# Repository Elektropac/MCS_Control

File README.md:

# MCS Control Firmware

Firmware til MCS Control-modulet.

## Hardware (v1)

- **Board:** Waveshare ESP32-S3-ETH
- **Chip:** ESP32-S3R8 (dual-core 240MHz, 512KB SRAM, 8MB PSRAM OPI)
- **Flash:** 16MB (W25Q128, QIO)
- **Ethernet:** W5500 via SPI (GPIO 11/12/13/14, RST=9, INT=10)
- **USB:** Type-C med CDC (upload + serial debug)
- **Produkt-link:** https://www.waveshare.com/esp32-s3-eth.htm
- **Wiki:** https://www.waveshare.com/wiki/ESP32-S3-ETH

## I2C Devices

| Address | Chip | Funktion |
|---------|------|----------|
| 0x21 | TCA9535 | Voltage select (5V/12V/24V) + HW/module version |
| 0x23 | TCA9535 | Input config channel B (analog front-end switches) |
| 0x25 | TCA9535 | Input config channel A (analog front-end switches) |
| 0x27 | TCA9535 | Serial control (RS-232/RS-485) + 2x relæ |
| 0x48 | ADS1115 | 16-bit ADC channel A (A1–A4) |
| 0x49 | ADS1115 | 16-bit ADC channel B (B1–B4) |

## Projektstruktur

```
src/
├── main.cpp              ← setup + FreeRTOS task start
├── board/                ← pin-definitions, board-specifikt
├── sampler/              ← 4 kHz ISR pulse sampling + flow guard
├── logging/              ← leveled log system (serial + ringbuffer)
├── debug/                ← diagnostik, serial commands, task registry
└── drivers/              ← hardware drivers
    ├── all_drivers_init  ← init af alt med probe + fejlhåndtering
    ├── hw_status         ← centralt register over hvad der er online
    ├── i2c               ← bus init + probe
    ├── voltage_select    ← spændingsvalg via 74HC139 demux
    ├── version           ← hardware + module version readout
    ├── serial_control    ← RS-232/RS-485 mode-skift
    ├── relays            ← 2x relæ kontrol
    ├── input_config      ← analog front-end switch kontrol
    ├── adc               ← ADS1115 voltage/mA/differential måling
    ├── buttons           ← 5-knap analog ladder
    ├── buzzer            ← PWM toner + melodier
    └── oled              ← SSD1306 128x64 display
```

## Arkitektur

### FreeRTOS (ikke custom scheduler)
Alt kører som selvstændige FreeRTOS tasks. Arduino's `loop()` er suspenderet.
FreeRTOS er standard på ESP32 og veldokumenteret — nemt for alle at læse op på.

### Memory-strategi
| Type | Bruges til |
|------|-----------|
| Intern SRAM (320 KB) | Tidskritisk: sampler, flow guard, drivers, task stacks |
| PSRAM (8 MB) | Ikke-tidskritisk: JSON parsing, interface-buffere (Niklas), store data |
| LittleFS (flash) | Persistent config (overlever genstart) |

Beslutning: Interface-laget (JSON kommunikation mellem Jesper/Niklas) allokerer buffere i PSRAM via `ps_malloc()`.
Tidskritisk kode bruger kun intern RAM.

### Memory reference

| Type | Størrelse | Hastighed | Volatile | Bruges til |
|------|-----------|-----------|----------|-----------|
| Internal SRAM | 320 KB | 1 clock cycle | Ja | Task stacks, variabler, buffere, FreeRTOS kernel |
| PSRAM (OPI) | 8 MB | ~10x langsommere (SPI) | Ja | Store buffere, JSON, data der ikke er tidskritisk |
| RTC SRAM | 16 KB | Hurtig | Overlever deep sleep | Variabler der skal overleve sleep (wake-up state) |
| Flash (XIP) | 16 MB | Langsom (cachet) | Nej | Firmware, LittleFS, NVS, OTA partitions |
| ↳ LittleFS | 5.8 MB | " | Nej | Filer (config JSON, logs, assets) |
| ↳ NVS | ~20 KB | " | Nej | Key-value store (WiFi creds, små config-værdier) |
| eFuse | 256 bytes | Engangslæs | Nej, permanent | MAC-adresse, security keys (read-only) |

**Tommelfingerregler:**
- Skal det være hurtigt → intern SRAM
- Skal det være stort → PSRAM
- Skal det overleve genstart → Flash (LittleFS eller NVS)
- Skal det overleve deep sleep → RTC SRAM

**Eksempler:**

```cpp
// --- Intern SRAM (default, alt normalt) ---
uint8_t buffer[256];                    // stack — automatisk intern
char* ptr = (char*)malloc(1024);        // heap — automatisk intern

// --- PSRAM (store ting, ikke tidskritisk) ---
char* json_buf = (char*)ps_malloc(8192);              // allokér 8 KB i PSRAM
uint8_t* big = (uint8_t*)heap_caps_malloc(50000, MALLOC_CAP_SPIRAM);  // eksplicit PSRAM

// --- RTC SRAM (overlever deep sleep) ---
RTC_DATA_ATTR uint32_t boot_count = 0;  // bevares gennem deep sleep cycles

// --- LittleFS (filer i flash, overlever genstart) ---
#include <LittleFS.h>
LittleFS.begin();
File f = LittleFS.open("/config.json", "r");
String content = f.readString();
f.close();

// --- NVS (key-value, overlever genstart) ---
#include <Preferences.h>
Preferences prefs;
prefs.begin("config", false);           // namespace "config"
prefs.putString("ssid", "MyWiFi");      // skriv
String ssid = prefs.getString("ssid");  // læs
prefs.end();
```

### TBD
- [ ] PSRAM-allocator til ArduinoJson — så `JsonDocument` automatisk bruger PSRAM uden rå pointers
- [ ] Function_silo: Byg kommando-register ud (relay_set, voltage_set, input_mode, adc_read, serial_mode, status, config_get/set)

## Toolchain

- PlatformIO (VS Code)
- Framework: Arduino
- Partition: Dual OTA (2x 5MB app) + LittleFS (5.8MB)

## Ansvarsfordeling

- **Jesper:** Hardware-lag — I/O, pulsmåling, relæer, sensorer, OLED/menu, lokal config/storage
- **Niklas:** Kommunikation — WiFi, Ethernet, BLE, USB serial, ESP-NOW, server-forbindelse

## Fejltolerance

Alle I2C-drivers probes ved boot. Hvis en chip ikke svarer:
- Den logges som fejl
- `hw_available()` returnerer false
- Driver-funktioner returnerer tidligt (0 / no-op)
- Systemet kører videre med det der virker

## Byg

1. Åbn mappen i VS Code med PlatformIO installeret
2. Build (flueben i bunden eller `pio run`)
3. Upload til board (pil i bunden eller `pio run -t upload`)
4. Serial Monitor: 115200 baud

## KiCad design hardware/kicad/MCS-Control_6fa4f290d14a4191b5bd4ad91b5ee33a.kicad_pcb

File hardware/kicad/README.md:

## PoE forenklet 2026-09-28

Ét nyt ark: **PoE_5V**, 5 V med mål op til 2 A, tegnet med direkte ledninger. De tidligere 5/12/24 V-ark er arkiveret i backup/PoE-41W-revA. PCB er uændret. Læs [PoE-design.md](PoE-design.md) om integration og resterende hardwarevalidering.

## DRC-oprydning efter import (2026-11-04, branch `hw/drc-oprydning`)

`hardware/tools/fix_easyeda_import.py` rydder importrester på BottomBoard uden at ændre forbindelser
(alle 938 pads har samme net før/efter; 0 uforbundne). DRC: **1352 → 522 fund**.

- Clearance-regel 0,15 mm (layoutet er lavet med EasyEDA's 6 mil) og kobber-til-kant 0,3 mm.
- 106 bundkomponenter havde courtyard på forsidens lag → flyttet til B.Courtyard.
- 312 pads (alle passive R/C/SD0805) havde pasta-margin −100 mm = ingen stencil-åbning → nulstillet.
- 14 spor med længde 0 fjernet.
- Relæspor (5 mm) `B_RELAY_NO`/`B_RELAY_COM` lå 0,14/0,20 mm fra højre kant → lodrette stykker rykket 0,5 mm ind (nu ~0,65/0,70 mm). DRC: **516 fund**, 0 kobber-til-kant.

**3D-visning rettet** (`hardware/tools/fix_3d_models.py`, kun model-felter):
- 18 PhotoMOS (SMD-8) manglede model på printet (kun sat i biblioteket) → tilføjet.
- 6 DC/DC (SIP-4 B2405S) pegede på en kopi af pin-header-modellen → KiCads Murata CRE1 (samme SIP-4-hus).
- EasyEDA placerer modeller efter midtpunkt, KiCad efter nulpunkt → klemrække U61, header J1, DC/DC drejet/flyttet
  så modellen dækker pads og courtyard.
- Relæ K1/K3 (EasyEDA-model ufuldstændig) og CN1/CN2 (model viste flerpolet klemme) → **forenklede kasser**
  i silketryk-omridsets mål (`3d/*.wrl`). Højde er skøn: relæ 20 mm, klemme 12 mm.
- **SMD-rotationer:** importen havde drejet mange modeller 90/180° (alle 144 R0603, 18 PhotoMOS, SOIC, SSOP,
  SMD-16, 6 SOT-23 på bunden). Rettet ved at finde den drejning hvor modellens benfødder (nederste
  STEP-hjørnepunkter) lander på pads — efterkontrol: 88–100 % for alle typer (SOP-4/SOP-8 kontrolleret visuelt).
- **U24 Waveshare ESP32-S3-ETH:** model tilføjet (`3d/waveshare_esp32s3eth.wrl`, fra control-emulator) — antager
  samme montering som pumpesimulatoren: ben loddet med 2,5 mm afstand, RJ45-siden op, USB ved printkanten.
- **LS1 buzzer (CPT-1667):** forenklet cylinder Ø16,6 mm, højde 8 mm (skøn).

**Tilbage — kræver manuel gennemgang:**
- **⚠ Isolationsslids mangler (250 V AC):** kom ikke med fra EasyEDA som udfræsning. I KiCad ligger kun
  midterlinjen på laget `IsolationSlot` (User.2, fræses IKKE) + HV-grænsen på bottom silk.
  Skal laves som **lukket udskæring på Edge.Cuts, 2 mm bred, runde ender**, langs IsolationSlot-stien:
  (169,09;155,12) → (169,09;149,41) → (176,45;142,04) → (176,45;140,65) → (178,99;138,10) → (178,99;133,79)
  → (182,80;129,98) → (182,80;91,24) → (184,58;89,46) → (193,47;89,46). Går bevidst ikke ud til kanten
  (4,9 mm fra underkant, 6,5 mm fra højre kant).
  Måling med slids: `A_RELAY_NO` ↔ `9-36V_IN` kun **2,56 mm luftafstand** hen over slidsen ved (170,7;152,1) —
  under typisk 3,0 mm for forstærket isolation → flyt 9-36V_IN-sporet ~0,5 mm. Øvrige HV↔LV ≥ 3,5 mm over
  slidsen; uden slids imellem ≥ 9,5 mm.
- 83 courtyard-overlap — **ACCEPTERET (beslutning 2026-11-04, Jesper):** courtyards er normale (~0,27 mm margin),
  komponenterne står reelt tæt: 0,30–0,5 mm pad-til-pad (ingen under 0,3 mm), kobber overholder 0,15 mm clearance.
  Printet er produceret og virker med denne placering → ingen flytning. Tætteste: D13/D14, D3/D4 (0,30 mm), R11/U20, R79/U44 (0,35 mm).
  Markeret som accepteret i `MCS-Control_…kicad_dru` (én regel pr. par, `severity ignore`). Nye overlap fanges stadig. DRC: **433 fund** (kun silk/kosmetik + 12 løse spor).
- 10× SOT-23 (2N7002) har courtyard *mindre* end egne pads (importfejl) — skjuler evt. overlap, giver ikke falske fund.
- 12 spor med løs ende (ikke fjernet automatisk — flere spor har samme net/længde, så en automatisk match kan ramme forkert).
- ~420 silk-advarsler og 2 tekst-tykkelser (kosmetisk).

# MCS-Control i KiCad

**Seneste ændring:** Sheet_3 er nu erstattet af et nyt W5500/Ethernet-diagram med 52 komponenter efter Waveshares reference. Det er udeladt fra PCB. Se [W5500-Sheet_3.md](W5500-Sheet_3.md) for omfang, grænseflade og kontrol. De øvrige ark og begge PCB-filer er uændrede. Importstatus nedenfor beskriver versionen før denne ændring.

Åbn `MCS-Control_6fa4f290d14a4191b5bd4ad91b5ee33a.kicad_pro`, og start Schematic Editor. Dobbeltklik på arkene i venstre side.

Projektet er importeret fra EasyEDA-backuppen den 28. september 2026. Alle syv kildeark er med samt et KiCad-oversigtsark. Sheet_2 var tomt i originalen; IO Expander indeholder en referencetabel som billede.

## Gennemført

- 276 komponenter overført med referencer og værdier.
- Lokale symbolbiblioteker og footprintbibliotek ligger i projektmappen.
- Siderammer og placering er tilpasset KiCad.
- Alle 973 tilsluttede ben i EasyEDAs officielle Protel-netliste har præcis samme forbindelsesgrupper i KiCad. KiCad viser desuden 66 isolerede ben.
- 274 komponenter har fået footprinttilknytning: 264 fra de oprindelige printlayouts og 10 modstande/kondensatorer genbruger samme kildes package-type. Padnumrene for de 264 direkte matches er kontrolleret mod symbolerne.
- BottomBoard er filen med projektets lange navn og endelsen `.kicad_pcb`. TopBoard er `Sapphire_Topboard.kicad_pcb`.

## Udestår før produktion eller automatisk PCB-opdatering

U32 (W5500) og X2 (25 MHz krystal) mangler footprints; de findes ikke på de to kildeprint. Der er ikke valgt erstatninger uden package-verifikation.

ERC giver 759 fund: 704 pin-type-konflikter, 29 uforbundne ben, 8 forsyningsben uden driver, 6 isolerede pin-labels, 6 ben uden driver, 4 netnavnekonflikter og 2 løse labels. Mange importerede symbolben har uspecificeret elektrisk type. Fundene er bevaret til elektrisk gennemgang; de er ikke skjult ved vilkårlige ændringer af pin-typer. Se `Importkontrol-ERC.rpt`.

Netlistematch dokumenterer bevarede forbindelser, ikke at originalkredsløbet er elektrisk korrekt. De to PCB-filer er importerede layouts; DRC, fremstillingsdata og diagram-til-PCB-synkronisering er ikke valideret. Diagrammet omfatter begge print, og komponentfordelingen skal håndteres inden brug af Update PCB from Schematic.

Behold hele mappen samlet, så de relative biblioteksstier virker.

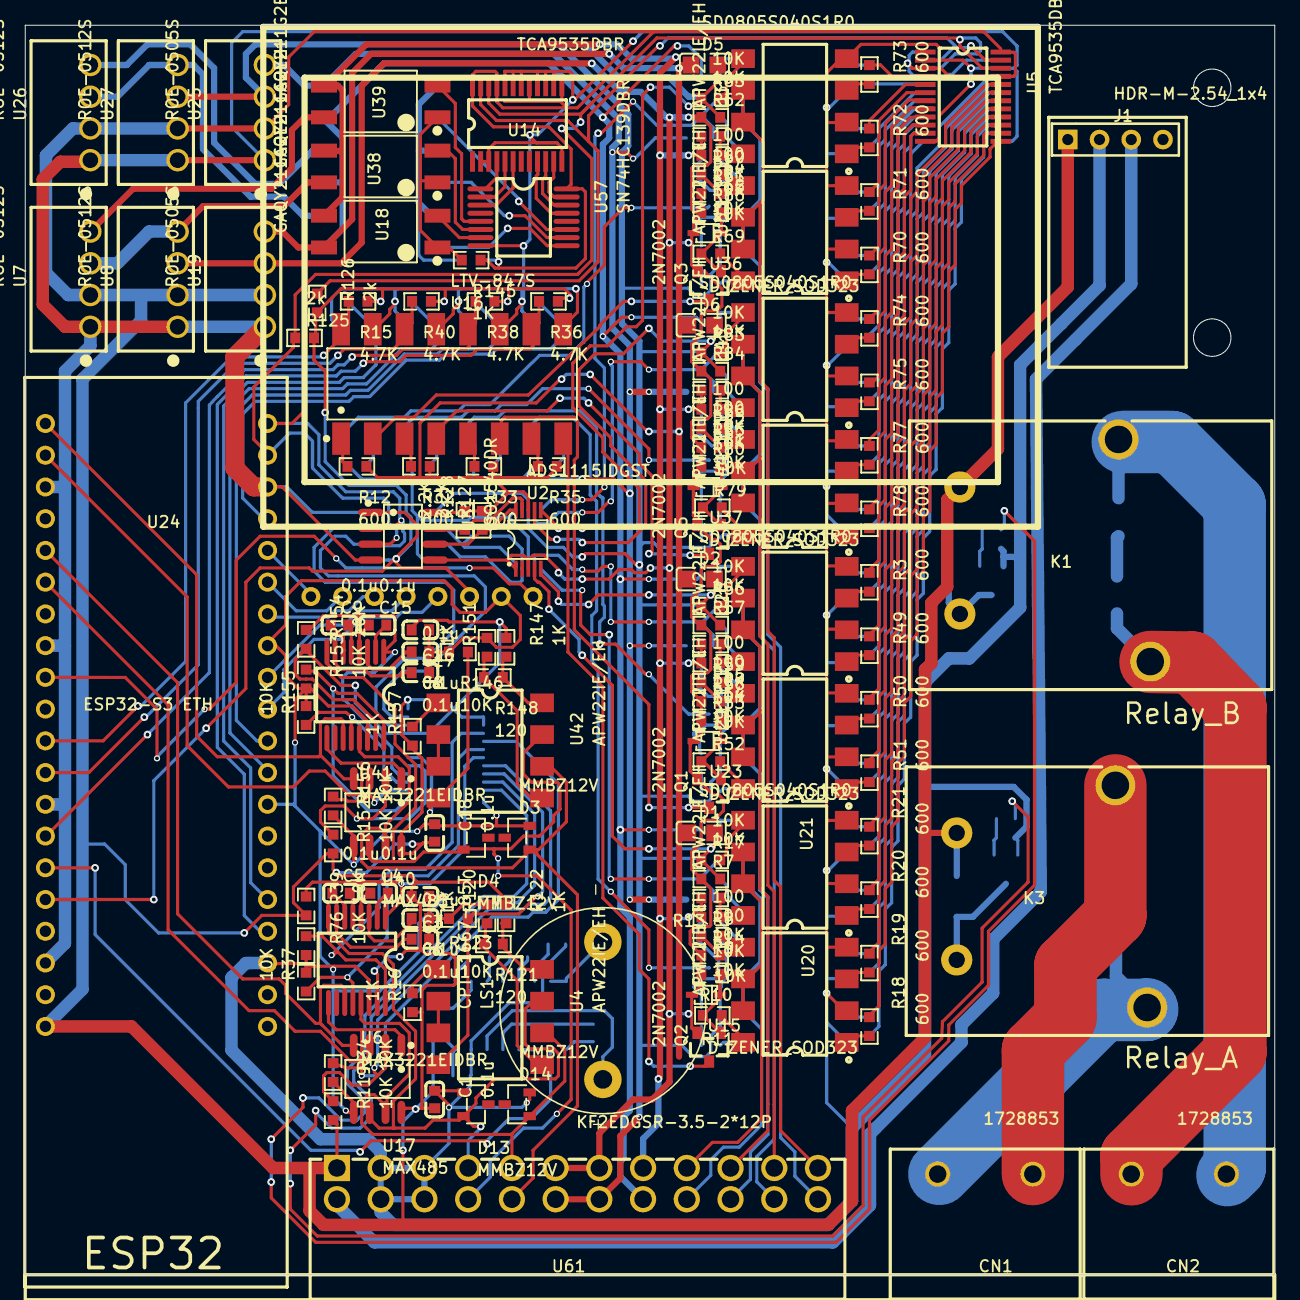
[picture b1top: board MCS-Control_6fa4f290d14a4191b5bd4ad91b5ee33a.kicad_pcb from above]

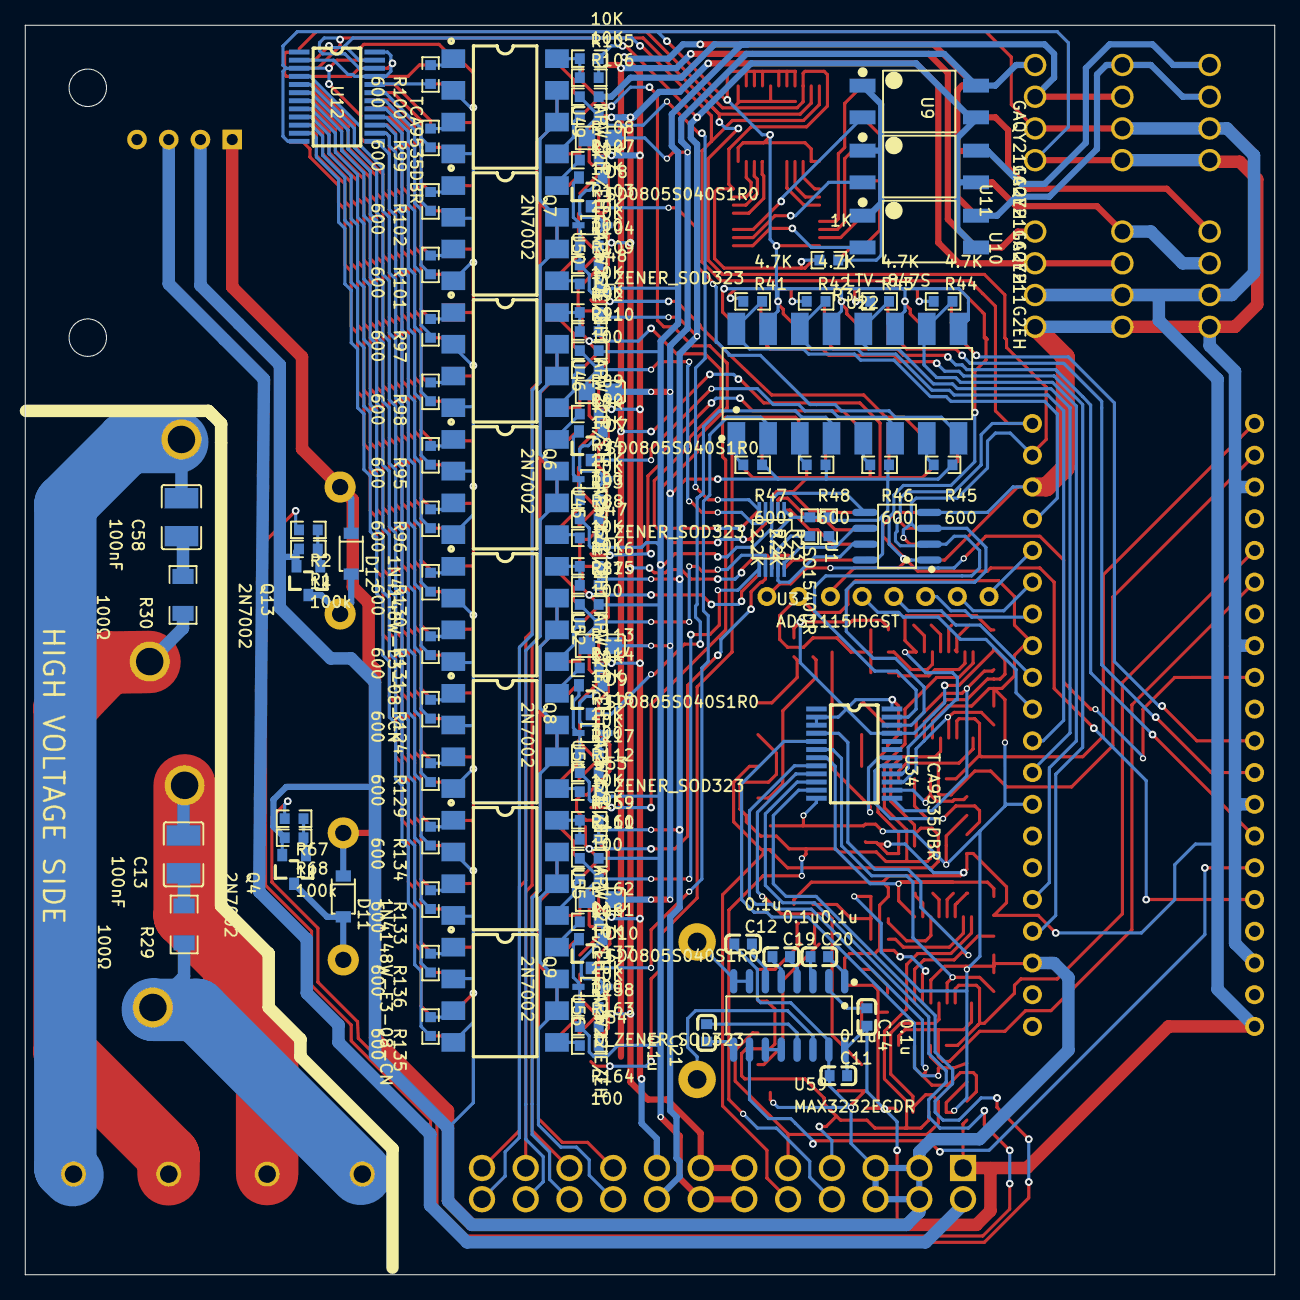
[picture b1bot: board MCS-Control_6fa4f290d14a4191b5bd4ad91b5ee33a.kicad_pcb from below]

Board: 2 copper layers, 100.0 x 100.0 mm, 262 parts (106 on the bottom side), 256 nets.

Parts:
C1, C2, C3, C4, C5, C6, C8, C9, C11, C12, C14, C15, C16, C17, C18, C19, C20, C21: 0.1u; C0603
C13, C58: 100nF; C1210
CN1, CN2: 1728853; CONN-TH_2P-P7.62_1728853
D1, D2, D5, D6, D7, D8, D9, D10: SD0805S040S1R0; D0805-RD
D3, D4, D13, D14: MMBZ12V; SOT-23-3_L2.9-W1.3-P1.90-LS2.4-BR
D11, D12: 1N4148W-E3-08-CN; SOD-123_L2.7-W1.6-LS3.7-RD
Hole_gge434084: Hole_gge434084
Hole_gge434114: Hole_gge434114
J1: HDR-M-2.54_1x4; HDR-M-2.54_1X4
K1, K3: T9GV1L14-5; RELAY-TH_TE_T9GV1L14-9
LS1: CPT-1667-85T; XDCR_CPT-1667-85T
Pad_gge404992: Pad_gge404992
Pad_gge405037: Pad_gge405037
Pad_gge405061: Pad_gge405061
Pad_gge405085: Pad_gge405085
Pad_gge405109: Pad_gge405109
Pad_gge405133: Pad_gge405133
Pad_gge405157: Pad_gge405157
Pad_gge405181: Pad_gge405181
Q1, Q2, Q3, Q4, Q5, Q6, Q7, Q8, Q9, Q13: 2N7002; SOT-23_L2.9-W1.3-P0.95-LS2.4-BR
R1, R68: 100k; R0603
R2, R67: 1k; R0603
R3, R12, R18, R19, R20, R21, R32, R33, R35, R45, R46, R47, R48, R49, R50, R51, R70, R71, R72, R73, R74, R75, R77, R78, R95, R96, R97, R98, R99, R100, R101, R102, R124, R129, R130, R131, R133, R134, R135, R136: 600; R0603
R7, R9, R10, R11, R13, R17, R34, R37, R39, R52, R53, R54, R55, R56, R57, R62, R63, R64, R65, R66, R69, R76, R79, R80, R81, R82, R83, R84, R89, R90, R91, R92, R93, R94, R103, R104, R105, R106, R107, R108, R113, R114, R115, R116, R117, R118, R119, R123, R137, R146, R152, R153, R154, R155, R156, R158, R159, R160, R161, R162: 10K; R0603
R8, R14, R58, R59, R60, R61, R85, R86, R87, R88, R109, R110, R111, R112, R163, R164: 100; R0603
R15, R36, R38, R40, R41, R42, R43, R44: 4.7K; R0603
R16, R31, R120, R122, R145, R147, R151, R157: 1K; R0603
R22, R23, R127, R128: 2.2K; R0603
R29, R30: 100Ω; R1206
R121, R148: 120; R0603
R125, R126: 2k; R0603
U1, U31: ISO1540DR; SOIC-8_L4.9-W3.9-P1.27-LS6.0-BL
U2, U3: ADS1115IDGST; VSSOP-10_L3.0-W3.0-P0.50-LS4.9-BL
U4, U20, U21, U28, U29, U33, U35, U42, U43, U44, U45, U46, U49, U50, U51, U52, U55, U56: APW22IE/EH; SMD-8_L9.8-W6.4-APW212G2EH
U5, U12, U14, U34: TCA9535DBR; TSSOP-24_L7.8-W4.4-P0.65-LS6.4-BL
U6, U41: MAX3221EIDBR; SSOP-16_L6.2-W5.3-P0.65-LS7.8-BL
U7, U8, U26, U27: ROE-0512S; SIP-4_L11.5-W6.0-P2.54-L_ROE-XXXXS
U9, U10, U11, U18, U38, U39: GAQY211G2EH; SOP-4_L6.4-W4.8-P2.54-LS10.2-BL
U15, U23, U36, U37, U47, U48, U53, U54: D_ZENER_SOD323; SOD-323_L1.6-W1.2-LS2.6-RD
U16, U22: LTV-847S; SMD-16_L20.0-W6.5-P2.54-LS10.2-BL
U17, U40: MAX485; SOP-8_L4.9-W3.9-P1.27-LS6.0-BL
U19, U25: ROE-0505S; SIP-4_L11.5-W6.0-P2.54-L_ROE-XXXXS
U24: ESP32-S3 ETH
U57: SN74HC139DBR; SSOP-16_L6.2-W5.3-P0.65-LS7.8-BL
U59: MAX3232ECDR; SOIC-16_L9.9-W3.9-P1.27-LS6.0-BL
U61: KF2EDGSR-3.5-2*12P; CONN-TH_24P-P3.50_KEFA_KF2EDGSR-3.5-2X12P

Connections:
9-36V_IN: J1.3, U61.2
+3V3: Pad_gge405133.1, R15.1, R36.1, R38.1, R40.1, R41.1, R42.1, R43.1, R44.1, R125.2, R126.2, U1.1, U24.36, U31.1
+5V: C1.2, C2.2, C11.2, C14.2, C17.2, C18.2, D11.1, D12.1, J1.1, K1.2, K3.2, R16.1, R31.1, R39.2, R119.2, R122.1, R145.1, R147.1, R152.2, R154.2, R157.1, U5.3, U5.21, U5.24, U6.15, U7.2, U8.2, U12.2, U12.21, U12.24, U14.13, U14.17, U14.21, U14.24, U17.8, U19.2, U24.40, U25.2, U26.2, U27.2, U34.2, U34.3, U34.21, U34.24, U40.8, U41.15, U57.16, U59.16, U61.1
A1_ANALOG_ADC: D1.2, R7.2, R17.1, U2.4
A1_DIGITAL_ISO: Q2.3, U16.8
A1_DIGITAL_MCU: R36.2, U16.10, U24.4
A1_FIELD_IN: U20.6, U20.7, U21.6, U21.7, U61.17
A1_SEL_ANALOG: R21.1, U5.16
A1_SEL_DIGITAL: R18.1, U5.13
A1_SEL_PULLUP: R20.1, U5.15
A1_SEL_SHUNT: R19.1, U5.14
A2_ANALOG_ADC: D2.2, R56.1, R57.2, U2.5
A2_DIGITAL_ISO: Q1.3, U16.6
A2_DIGITAL_MCU: R38.2, U16.12, U24.34
A2_FIELD_IN: U28.6, U28.7, U29.6, U29.7, U61.19
A2_SEL_ANALOG: R3.1, U5.20
A2_SEL_DIGITAL: R51.1, U5.17
A2_SEL_PULLUP: R49.1, U5.19
A2_SEL_SHUNT: R50.1, U5.18
A3_ANALOG_ADC: D6.2, R83.1, R84.2, U2.7
A3_DIGITAL_ISO: Q5.3, U16.4
A3_DIGITAL_MCU: R40.2, U16.14, U24.32
A3_FIELD_IN: U43.6, U43.7, U44.6, U44.7, U61.21
A3_SEL_ANALOG: R74.1, U5.8
A3_SEL_DIGITAL: R78.1, U5.11
A3_SEL_PULLUP: R75.1, U5.9
A3_SEL_SHUNT: R77.1, U5.10
A4_ANALOG_ADC: D5.2, R62.2, R63.1, U2.6
A4_DIGITAL_ISO: Q3.3, U16.2
A4_DIGITAL_MCU: R15.2, U16.16, U24.31
A4_FIELD_IN: U33.6, U33.7, U35.6, U35.7, U61.23
A4_SEL_ANALOG: R73.1, U5.4
A4_SEL_DIGITAL: R70.1, U5.7
A4_SEL_PULLUP: R72.1, U5.5
A4_SEL_SHUNT: R71.1, U5.6
A_485_A/232_TX: D13.2, U4.7, U6.8, U17.6, U61.7
A_485_B/232_RX: D14.1, U4.6, U6.13, U17.7, U61.9
A_ISO_5V: D1.1, D2.1, D5.1, D6.1, R12.1, R32.1, R33.1, R35.1, R127.2, R128.2, U2.8, U18.4, U19.4, U31.8
A_ISO_5V/12V/24V: R9.2, R13.2, R54.2, R55.2, R64.2, R65.2, R81.2, R82.2, U18.3, U38.3, U39.3, U61.15
A_ISO_GND: Q1.2, Q2.2, Q3.2, Q5.2, R7.1, R10.1, R14.1, R53.1, R57.1, R58.1, R61.1, R62.1, R66.1, R80.1, R84.1, R85.1, U2.1, U2.3, U8.3, U15.2, U19.3, U23.2, U31.5, U36.2, U37.2, U61.11, U61.13
A_REALY_SWITCH: R67.2, U34.10
A_RELAY_COM: C13.2, CN1.2, K3.1
A_RELAY_NO: CN1.1, K3.4, R29.1
B1_ANALOG_ADC: D10.2, R161.1, R162.2, U3.6
B1_DIGITAL_ISO: Q9.3, U22.2
B1_DIGITAL_MCU: R41.2, U22.16, U24.17
B1_FIELD_IN: U55.6, U55.7, U56.6, U56.7, U61.18
B1_SEL_ANALOG: R133.1, U12.9
B1_SEL_DIGITAL: R136.1, U12.10
B1_SEL_PULLUP: R134.1, U12.8
B1_SEL_SHUNT: R135.1, U12.11
B2_ANALOG_ADC: D9.2, R113.2, R114.1, U3.7
B2_DIGITAL_ISO: Q8.3, U22.4
B2_DIGITAL_MCU: R42.2, U22.14, U24.10
B2_FIELD_IN: U51.6, U51.7, U52.6, U52.7, U61.20
B2_SEL_ANALOG: R131.1, U12.5
B2_SEL_DIGITAL: R124.1, U12.6
B2_SEL_PULLUP: R130.1, U12.4
B2_SEL_SHUNT: R129.1, U12.7
B3_ANALOG_ADC: D7.2, R89.2, R90.1, U3.4
B3_DIGITAL_ISO: Q6.3, U22.6
B3_DIGITAL_MCU: R43.2, U22.12, U24.9
B3_FIELD_IN: U45.6, U45.7, U46.6, U46.7, U61.22
B3_SEL_ANALOG: R98.1, U12.15
B3_SEL_DIGITAL: R95.1, U12.14
B3_SEL_PULLUP: R97.1, U12.16
B3_SEL_SHUNT: R96.1, U12.13
B4_ANALOG_ADC: D8.2, R107.1, R108.2, U3.5
B4_DIGITAL_ISO: Q7.3, U22.8
B4_DIGITAL_MCU: R44.2, U22.10, U24.5
B4_FIELD_IN: U49.6, U49.7, U50.6, U50.7, U61.24
B4_SEL_ANALOG: R99.1, U12.19
B4_SEL_DIGITAL: R102.1, U12.18
B4_SEL_PULLUP: R100.1, U12.20
B4_SEL_SHUNT: R101.1, U12.17
BUTTONPRESS: Pad_gge405181.1, U24.29
BUZZER: U24.35, U59.10
B_485_A/232_TX: D4.2, U40.6, U41.8, U42.7, U61.8
B_485_B/232_RX: D3.1, U40.7, U41.13, U42.6, U61.10
B_ISO_5V: D7.1, D8.1, D9.1, D10.1, R22.2, R23.2, R45.1, R46.1, R47.1, R48.1, U1.8, U3.1, U3.8, U9.4, U25.4
B_ISO_5V/12V/24V: R91.2, R92.2, R105.2, R106.2, R115.2, R116.2, R159.2, R160.2, U9.3, U10.3, U11.3, U61.16
B_ISO_GND: Q6.2, Q7.2, Q8.2, Q9.2, R88.1, R89.1, R93.1, R104.1, R108.1, R109.1, R112.1, R113.1, R117.1, R158.1, R162.1, R163.1, U1.5, U3.3, U25.3, U27.3, U47.2, U48.2, U53.2, U54.2, U61.12, U61.14
B_REALY_SWITCH: R2.2, U34.11
B_RELAY_COM: C58.2, CN2.2, K1.1
B_RELAY_NO: CN2.1, K1.4, R30.1
C3_1: C3.1, U6.7
C4_1: C4.1, U6.4
C4_2: C4.2, U6.2
C5_1: C5.1, U6.6
C5_2: C5.2, U6.5
C6_2: C6.2, U6.3
C13_1: C13.1, R29.2
C58_1: C58.1, R30.2
CLK: Pad_gge405061.1, U24.14
CONTROL_A_5V: U18.2, U57.7
CONTROL_A_12V: U38.2, U57.6
CONTROL_A_24V: U39.2, U57.5
CONTROL_B_5V: U9.2, U57.11
CONTROL_B_12V: U10.2, U57.9
CONTROL_B_24V: U11.2, U57.10
CS: Pad_gge404992.1, U24.16
DC: Pad_gge405109.1, U24.11
DE-CHA: R34.1, U17.3, U34.5
DE-CHB: R156.1, U34.14, U40.3
DIN: Pad_gge405037.1, U24.15
EN#-CHA: R39.1, U6.1, U34.7
EN#-CHB: R154.1, U34.16, U41.1
ENABLEVOLTAGE_A: U14.6, U57.3
ENABLEVOLTAGE_B: U14.11, U57.15
FORCEOFF#-CHA: R76.1, U6.16, U34.4
FORCEOFF#-CHB: R153.1, U34.13, U41.16
FORCEON-CHA: R37.1, U6.12, U34.6
FORCEON-CHB: R155.1, U34.15, U41.12
GND: C1.1, C2.1, C3.2, C6.1, C8.1, C11.1, C12.1, C16.2, C17.1, C18.1, D3.2, D4.1, D13.1, D14.2, J1.2, Pad_gge405157.1, Q4.2, Q13.2, R1.2, R34.2, R37.2, R68.2, R76.2, R120.2, R123.2, R146.2, R151.2, R153.2, R155.2, R156.2, U1.4, U5.2, U5.12, U6.14, U7.1, U8.1, U12.3, U12.12, U14.2, U14.3, U14.12, U14.14, U14.15, U14.16, U14.18, U14.19, U14.20, U16.9, U16.11, U16.13, U16.15, U17.5, U19.1, U20.2, U20.4, U21.2, U21.4, U22.9, U22.11, U22.13, U22.15, U24.3, U24.8, U24.13, U24.18, U24.23, U24.28, U24.33, U24.38, U25.1, U26.1, U27.1, U28.2, U28.4, U29.2, U29.4, U31.4, U33.2, U33.4, U34.12, U35.2, U35.4, U40.5, U41.14, U43.2, U43.4, U44.2, U44.4, U45.2, U45.4, U46.2, U46.4, U49.2, U49.4, U50.2, U50.4, U51.2, U51.4, U52.2, U52.4, U55.2, U55.4, U56.2, U56.4, U57.8, U59.15, U61.3, U61.4, U61.5, U61.6
K1_3: D12.2, K1.3, Q13.3
K3_3: D11.2, K3.3, Q4.3
Q4_1: Q4.1, R67.1, R68.1
R1_1: Q13.1, R1.1, R2.1
R9_1: R9.1, R13.1, U21.8
R11_2: R11.2, U20.8
R12_2: R12.2, U16.1
R14_2: R8.1, R14.2
R16_2: R16.2, U4.1
R17_2: R17.2, U21.5
R18_2: R18.2, U20.1
R19_2: R19.2, U20.3
R20_2: R20.2, U21.1
R21_2: R21.2, U21.3
R32_2: R32.2, U16.3
R33_2: R33.2, U16.5
R35_2: R35.2, U16.7
R53_2: Q1.1, R52.1, R53.2, U23.1
R59_1: R58.2, R59.1
R59_2: R59.2, U29.5
R61_2: R60.1, R61.2
R63_2: R63.2, U35.5
R65_1: R64.1, R65.1, U35.8
R69_2: R69.2, U33.8
R70_2: R70.2, U33.1
R71_2: R71.2, U33.3
R72_2: R72.2, U35.1
R73_2: R73.2, U35.3
R80_2: Q5.1, R79.1, R80.2, U37.1
R86_1: R85.2, R86.1
R86_2: R86.2, U44.5
R88_2: R87.1, R88.2
R90_2: R90.2, U46.5
R92_1: R91.1, R92.1, U46.8
R94_2: R94.2, U45.8
R95_2: R95.2, U45.1
R96_2: R96.2, U45.3
R97_2: R97.2, U46.1
R98_2: R98.2, U46.3
R104_2: Q7.1, R103.1, R104.2, U48.1
R110_1: R109.2, R110.1
R110_2: R110.2, U50.5
R112_2: R111.1, R112.2
R114_2: R114.2, U52.5
R116_1: R115.1, R116.1, U52.8
R118_2: R118.2, U51.8
R124_2: R124.2, U51.1
R129_2: R129.2, U51.3
R130_2: R130.2, U52.1
R131_2: R131.2, U52.3
R147_2: R147.2, R148.1, U42.8
R148_2: R148.2, R151.1, U42.5
R158_2: Q9.1, R137.1, R158.2, U54.1
R164_1: R163.2, R164.1
R164_2: R164.2, U56.5
RE#-CHA: R119.1, U17.2, U34.8
RE#-CHB: R152.1, U34.17, U40.2
RS485_TERM_BIAS_EN_N_CHA: R123.1, U4.4, U34.9
RS485_TERM_BIAS_EN_N_CHB: R146.1, U34.18, U42.4
RST: Pad_gge405085.1, U24.12
SCL1: R125.1, U1.3, U5.22, U12.22, U14.22, U24.19, U31.3, U34.22
SCL_2_A: R127.1, U2.10, U31.6
SCL_2_B: R23.1, U1.6, U3.10
SDA1: R126.1, U1.2, U5.23, U12.23, U14.23, U24.20, U31.2, U34.23
SDA_2_A: R128.1, U2.9, U31.7
SDA_2_B: R22.1, U1.7, U3.9
SETVOLTAGE1_A: U14.5, U57.2
SETVOLTAGE1_B: U14.10, U57.14
SETVOLTAGE2_A: U14.4, U57.1
SETVOLTAGE2_B: U14.9, U57.13
U4_2: U4.2, U4.3
U4_5: R120.1, R121.2, U4.5
U4_8: R121.1, R122.2, U4.8
U7_4: U7.4, U39.4
U8_4: U7.3, U8.4, U38.4
U9_1: R31.2, U9.1, U10.1, U11.1
U10_4: U10.4, U26.3, U27.4
U11_4: U11.4, U26.4
U15_1: Q2.1, R10.2, R11.1, U15.1
U20_5: R8.2, U20.5
U22_1: R47.2, U22.1
U22_3: R48.2, U22.3
U22_5: R46.2, U22.5
U22_7: R45.2, U22.7
U28_1: R49.2, U28.1
U28_3: R3.2, U28.3
U28_5: R56.2, U28.5
U28_8: R54.1, R55.1, U28.8
U29_1: R51.2, U29.1
U29_3: R50.2, U29.3
U29_8: R52.2, U29.8
U33_5: R60.2, U33.5
U36_1: Q3.1, R66.2, R69.1, U36.1
U39_1: R145.2, U18.1, U38.1, U39.1
U41_2: C15.2, U41.2
U41_3: C8.2, U41.3
U41_4: C15.1, U41.4
U41_5: C9.2, U41.5
U41_6: C9.1, U41.6
U41_7: C16.1, U41.7
U42_1: R157.2, U42.1
U42_2: U42.2, U42.3
U43_1: R75.2, U43.1
U43_3: R74.2, U43.3
U43_5: R83.2, U43.5
U43_8: R81.1, R82.1, U43.8
U44_1: R78.2, U44.1
U44_3: R77.2, U44.3
U44_8: R79.2, U44.8
U45_5: R87.2, U45.5
U47_1: Q6.1, R93.2, R94.1, U47.1
U49_1: R100.2, U49.1
U49_3: R99.2, U49.3
U49_5: R107.2, U49.5
U49_8: R105.1, R106.1, U49.8
U50_1: R102.2, U50.1
U50_3: R101.2, U50.3
U50_8: R103.2, U50.8
U51_5: R111.2, U51.5
U53_1: Q8.1, R117.2, R118.1, U53.1
U55_1: R134.2, U55.1
U55_3: R133.2, U55.3
U55_5: R161.2, U55.5
U55_8: R159.1, R160.1, U55.8
U56_1: R136.2, U56.1
U56_3: R135.2, U56.3
U56_8: R137.2, U56.8
U59_1: C20.2, U59.1
U59_2: C14.1, U59.2
U59_3: C20.1, U59.3
U59_4: C19.2, U59.4
U59_5: C19.1, U59.5
U59_6: C12.2, U59.6
U59_7: LS1.N, U59.7, U59.8
U59_9: C21.1, U59.9
U59_11: U59.11, U59.12
U59_13: C21.2, U59.13
U59_14: LS1.P, U59.14
UART-A-RX: U6.9, U17.1, U24.26
UART-A-TX: U6.11, U17.4, U24.25
UART-B-RX: U24.22, U40.1, U41.9
UART-B-TX: U24.21, U40.4, U41.11

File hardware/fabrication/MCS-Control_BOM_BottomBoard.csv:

Designator,Value,Footprint,Qty,Manufacturer,Note
C1,0.1u,C1,1,Samsung,
C2,0.1u,C2,1,Samsung,
C3,0.1u,C3,1,Samsung,
C4,0.1u,C4,1,Samsung,
C5,0.1u,C5,1,Samsung,
C6,0.1u,C6,1,Samsung,
C8,0.1u,C8,1,Samsung,
C9,0.1u,C9,1,Samsung,
C11,0.1u,C11,1,,
C12,0.1u,C12,1,,
C13,100nF,C13,1,KEMET,
C14,0.1u,C14,1,,
C15,0.1u,C15,1,Samsung,
C16,0.1u,C16,1,Samsung,
C17,0.1u,C17,1,Samsung,
C18,0.1u,C18,1,Samsung,
C19,0.1u,C19,1,,
C20,0.1u,C20,1,,
C21,0.1u,C21,1,,
C58,100nF,C58,1,KEMET,
CN1,1728853,CN1,1,Phoenix Contact,
CN2,1728853,CN2,1,Phoenix Contact,
D1,SD0805S040S1R0,D1,1,Kyocera AVX,
D2,SD0805S040S1R0,D2,1,Kyocera AVX,
D3,MMBZ12V,D3,1,onsemi,
D4,MMBZ12V,D4,1,onsemi,
D5,SD0805S040S1R0,D5,1,Kyocera AVX,
D6,SD0805S040S1R0,D6,1,Kyocera AVX,
D7,SD0805S040S1R0,D7,1,Kyocera AVX,
D8,SD0805S040S1R0,D8,1,Kyocera AVX,
D9,SD0805S040S1R0,D9,1,Kyocera AVX,
D10,SD0805S040S1R0,D10,1,Kyocera AVX,
D11,1N4148W-E3-08-CN,D11,1,ChipNobo,
D12,1N4148W-E3-08-CN,D12,1,ChipNobo,
D13,MMBZ12V,D13,1,onsemi,
D14,MMBZ12V,D14,1,onsemi,
J1,HDR-M-2.54_1x4,J1,1,,
K1,T9GV1L14-5,K1,1,TE Connectivity,
K3,T9GV1L14-5,K3,1,TE Connectivity,
LS1,CPT-1667-85T,LS1,1,,
Q1,2N7002,Q1,1,Nexperia,
Q2,2N7002,Q2,1,Nexperia,
Q3,2N7002,Q3,1,Nexperia,
Q4,2N7002,Q4,1,Nexperia,
Q5,2N7002,Q5,1,Nexperia,
Q6,2N7002,Q6,1,Nexperia,
Q7,2N7002,Q7,1,Nexperia,
Q8,2N7002,Q8,1,Nexperia,
Q9,2N7002,Q9,1,Nexperia,
Q13,2N7002,Q13,1,Nexperia,
R1,100k,R1,1,,
R2,1k,R2,1,,
R3,600,R3,1,,
R7,10K,R7,1,,
R8,100,R8,1,,
R9,10K,R9,1,,
R10,10K,R10,1,,
R11,10K,R11,1,,
R12,600,R12,1,,
R13,10K,R13,1,,
R14,100,R14,1,,
R15,4.7K,R15,1,,
R16,1K,R16,1,,
R17,10K,R17,1,,
R18,600,R18,1,,
R19,600,R19,1,,
R20,600,R20,1,,
R21,600,R21,1,,
R22,2.2K,R22,1,,
R23,2.2K,R23,1,,
R29,100Ω,R29,1,Ohmite,
R30,100Ω,R30,1,Ohmite,
R31,1K,R31,1,,
R32,600,R32,1,,
R33,600,R33,1,,
R34,10K,R34,1,,
R35,600,R35,1,,
R36,4.7K,R36,1,,
R37,10K,R37,1,,
R38,4.7K,R38,1,,
R39,10K,R39,1,,
R40,4.7K,R40,1,,
R41,4.7K,R41,1,,
R42,4.7K,R42,1,,
R43,4.7K,R43,1,,
R44,4.7K,R44,1,,
R45,600,R45,1,,
R46,600,R46,1,,
R47,600,R47,1,,
R48,600,R48,1,,
R49,600,R49,1,,
R50,600,R50,1,,
R51,600,R51,1,,
R52,10K,R52,1,,
R53,10K,R53,1,,
R54,10K,R54,1,,
R55,10K,R55,1,,
R56,10K,R56,1,,
R57,10K,R57,1,,
R58,100,R58,1,,
R59,100,R59,1,,
R60,100,R60,1,,
R61,100,R61,1,,
R62,10K,R62,1,,
R63,10K,R63,1,,
R64,10K,R64,1,,
R65,10K,R65,1,,
R66,10K,R66,1,,
R67,1k,R67,1,,
R68,100k,R68,1,,
R69,10K,R69,1,,
R70,600,R70,1,,
R71,600,R71,1,,
R72,600,R72,1,,
R73,600,R73,1,,
R74,600,R74,1,,
R75,600,R75,1,,
R76,10K,R76,1,,
R77,600,R77,1,,
R78,600,R78,1,,
R79,10K,R79,1,,
R80,10K,R80,1,,
R81,10K,R81,1,,
R82,10K,R82,1,,
R83,10K,R83,1,,
R84,10K,R84,1,,
R85,100,R85,1,,
R86,100,R86,1,,
R87,100,R87,1,,
R88,100,R88,1,,
R89,10K,R89,1,,
R90,10K,R90,1,,
R91,10K,R91,1,,
R92,10K,R92,1,,
R93,10K,R93,1,,
R94,10K,R94,1,,
R95,600,R95,1,,
R96,600,R96,1,,
R97,600,R97,1,,
R98,600,R98,1,,
R99,600,R99,1,,
R100,600,R100,1,,
R101,600,R101,1,,
R102,600,R102,1,,
R103,10K,R103,1,,
R104,10K,R104,1,,
R105,10K,R105,1,,
R106,10K,R106,1,,
R107,10K,R107,1,,
R108,10K,R108,1,,
R109,100,R109,1,,
R110,100,R110,1,,
R111,100,R111,1,,
R112,100,R112,1,,
R113,10K,R113,1,,
R114,10K,R114,1,,
R115,10K,R115,1,,
R116,10K,R116,1,,
R117,10K,R117,1,,
R118,10K,R118,1,,
R119,10K,R119,1,,
R120,1K,R120,1,,
R121,120,R121,1,,
R122,1K,R122,1,,
R123,10K,R123,1,,
R124,600,R124,1,,
R125,2k,R125,1,,
R126,2k,R126,1,,
R127,2.2K,R127,1,,
R128,2.2K,R128,1,,
R129,600,R129,1,,
R130,600,R130,1,,
R131,600,R131,1,,
R133,600,R133,1,,
R134,600,R134,1,,
R135,600,R135,1,,
R136,600,R136,1,,
R137,10K,R137,1,,
R145,1K,R145,1,,
R146,10K,R146,1,,
R147,1K,R147,1,,
R148,120,R148,1,,
R151,1K,R151,1,,
R152,10K,R152,1,,
R153,10K,R153,1,,
R154,10K,R154,1,,
R155,10K,R155,1,,
R156,10K,R156,1,,
R157,1K,R157,1,,
R158,10K,R158,1,,
R159,10K,R159,1,,
R160,10K,R160,1,,
R161,10K,R161,1,,
R162,10K,R162,1,,
R163,100,R163,1,,
R164,100,R164,1,,
U1,ISO1540DR,U1,1,TI,
U2,ADS1115IDGST,U2,1,TI,
U3,ADS1115IDGST,U3,1,TI,
U4,APW22IE/EH,U4,1,APSEMI,
U5,TCA9535DBR,U5,1,Texas Instruments,
U6,MAX3221EIDBR,U6,1,Texas Instruments,
U7,ROE-0512S,U7,1,YLPTEC,
U8,ROE-0512S,U8,1,YLPTEC,
U9,GAQY211G2EH,U9,1,SUPSiC,
U10,GAQY211G2EH,U10,1,SUPSiC,
U11,GAQY211G2EH,U11,1,SUPSiC,
U12,TCA9535DBR,U12,1,Texas Instruments,
U14,TCA9535DBR,U14,1,Texas Instruments,
U15,D_ZENER_SOD323,U15,1,null,
U16,LTV-847S,U16,1,LITEON,
U17,MAX485,U17,1,ElecSuper,
U18,GAQY211G2EH,U18,1,SUPSiC,
U19,ROE-0505S,U19,1,YLPTEC,
U20,APW22IE/EH,U20,1,APSEMI,
U21,APW22IE/EH,U21,1,APSEMI,
U22,LTV-847S,U22,1,LITEON,
U23,D_ZENER_SOD323,U23,1,null,
U24,ESP32-S3 ETH,U24,1,,MONTERES IKKE (ESP32-modul sættes i separat)
U25,ROE-0505S,U25,1,YLPTEC,
U26,ROE-0512S,U26,1,YLPTEC,
U27,ROE-0512S,U27,1,YLPTEC,
U28,APW22IE/EH,U28,1,APSEMI,
U29,APW22IE/EH,U29,1,APSEMI,
U31,ISO1540DR,U31,1,TI,
U33,APW22IE/EH,U33,1,APSEMI,
U34,TCA9535DBR,U34,1,Texas Instruments,
U35,APW22IE/EH,U35,1,APSEMI,
U36,D_ZENER_SOD323,U36,1,null,
U37,D_ZENER_SOD323,U37,1,null,
U38,GAQY211G2EH,U38,1,SUPSiC,
U39,GAQY211G2EH,U39,1,SUPSiC,
U40,MAX485,U40,1,ElecSuper,
U41,MAX3221EIDBR,U41,1,Texas Instruments,
U42,APW22IE/EH,U42,1,APSEMI,
U43,APW22IE/EH,U43,1,APSEMI,
U44,APW22IE/EH,U44,1,APSEMI,
U45,APW22IE/EH,U45,1,APSEMI,
U46,APW22IE/EH,U46,1,APSEMI,
U47,D_ZENER_SOD323,U47,1,null,
U48,D_ZENER_SOD323,U48,1,null,
U49,APW22IE/EH,U49,1,APSEMI,
U50,APW22IE/EH,U50,1,APSEMI,
U51,APW22IE/EH,U51,1,APSEMI,
U52,APW22IE/EH,U52,1,APSEMI,
U53,D_ZENER_SOD323,U53,1,null,
U54,D_ZENER_SOD323,U54,1,null,
U55,APW22IE/EH,U55,1,APSEMI,
U56,APW22IE/EH,U56,1,APSEMI,
U57,SN74HC139DBR,U57,1,TI,
U59,MAX3232ECDR,U59,1,TI,
U61,KF2EDGSR-3.5-2*12P,U61,1,null,

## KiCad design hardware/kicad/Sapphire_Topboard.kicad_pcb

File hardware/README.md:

# MCS Control — Hardware (KiCad)

PCB- og schematic-filer for MCS Control, konverteret fra det oprindelige EasyEDA Pro-projekt til KiCad.

## Åbn projektet

Åbn `kicad/MCS-Control_6fa4f290d14a4191b5bd4ad91b5ee33a.kicad_pro` i KiCad og start Schematic Editor.
Hold hele `kicad/`-mappen samlet — de lokale symbol-/footprint-biblioteker peges på via relative stier
(`sym-lib-table` / `fp-lib-table`).

## Boards

- **BottomBoard:** `kicad/MCS-Control_6fa4f290d14a4191b5bd4ad91b5ee33a.kicad_pcb`
- **TopBoard:** `kicad/Sapphire_Topboard.kicad_pcb`

Schematic'et dækker begge print. Komponentfordelingen mellem de to boards skal håndteres **før**
"Update PCB from Schematic" bruges.

## Status efter konvertering (EasyEDA → KiCad, 28/9 2026)

Verificeret OK:
- 276 komponenter overført med referencer + værdier.
- Alle 973 forbundne ben matcher 1:1 mod EasyEDAs officielle Protel-netliste (forbindelser intakte).
- 274/276 komponenter har footprint. Lokale symbol- + footprint-biblioteker ligger i mappen.
- W5500- og PoE-delkontroller: ingen net-mismatch, ingen dublet-referencer.

Udestår før produktion:
- **U32 (W5500)** og **X2 (25 MHz krystal)** mangler footprints (fandtes ikke på kildeprintene).
- **ERC: 759 fund** — hovedsagelig importartefakter (uspecificeret elektrisk pin-type på importerede
  symboler), ikke nødvendigvis reelle fejl. Skal gennemgås, ikke skjules. Se `kicad/Importkontrol-ERC.rpt`.
- **PCB ikke valideret:** DRC, fremstillingsdata og schematic→PCB-sync er ikke kørt.
- **W5500/Ethernet-ark (Sheet_3)** er tegnet (52 komponenter, Waveshare-reference) men bevidst udeladt fra PCB.

## PoE

Aktuel PoE-forsyning: **PoE_5V** (5 V, op til ~2 A). Se `kicad/PoE-design.md`.
Den tidligere 24 V / 41 W-variant er arkiveret i `kicad/backup/PoE-41W-revA/`.

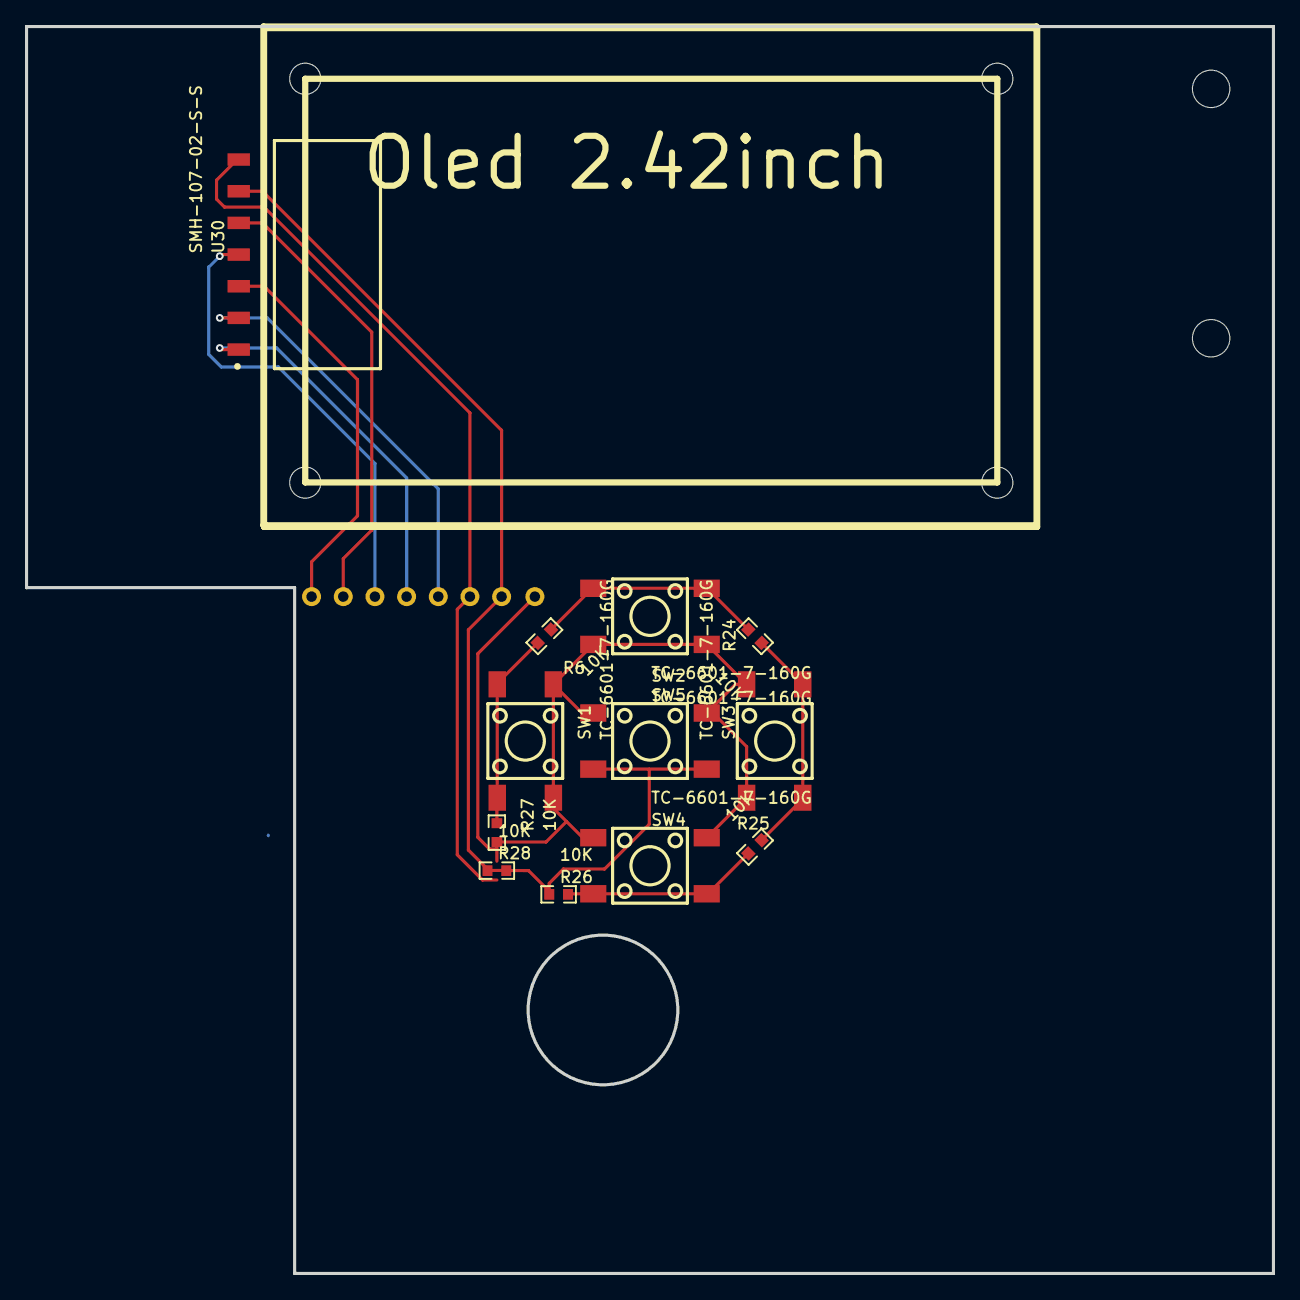
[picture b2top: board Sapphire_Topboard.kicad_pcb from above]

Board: 2 copper layers, 100.0 x 100.0 mm, 26 parts (0 on the bottom side), 12 nets.

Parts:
Hole_gge50749: Hole_gge50749
Hole_gge50779: Hole_gge50779
Hole_gge176522: Hole_gge176522
Hole_gge176537: Hole_gge176537
Hole_gge176552: Hole_gge176552
Hole_gge176567: Hole_gge176567
Pad_gge174991: Pad_gge174991
Pad_gge175015: Pad_gge175015
Pad_gge175039: Pad_gge175039
Pad_gge175063: Pad_gge175063
Pad_gge175087: Pad_gge175087
Pad_gge175111: Pad_gge175111
Pad_gge175135: Pad_gge175135
Pad_gge175159: Pad_gge175159
R6, R24, R25, R26, R27, R28: 10K; R0603
SW1, SW2, SW3, SW4, SW5: TC-6601-7-160G; SW-SMD_4P-L6.0-W6.0-P4.50-LS10.0_TL3301EF160QG
U30: SMH-107-02-S-S; HDR-SMD_7P-P2.54_SMH-107-02-S-S

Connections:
+3V3: Pad_gge175111.1, R28.2, U30.7
BUTTONPRESS: Pad_gge175159.1, R27.2, R28.1, SW1.1, SW1.2, SW2.1, SW2.2, SW3.1, SW3.2, SW4.1, SW4.2, SW5.1, SW5.2
CLK: Pad_gge175039.1, U30.4
CS: Pad_gge174991.1, U30.3
DC: Pad_gge175087.1, U30.2
DIN: Pad_gge175015.1, U30.5
GND: Pad_gge175135.1, R26.1, SW5.3, SW5.4, U30.6
R6_1: R6.1, R24.2, SW2.3, SW2.4
R6_2: R6.2, R27.1, SW1.3, SW1.4
R24_1: R24.1, R25.2, SW3.3, SW3.4
R25_1: R25.1, R26.2, SW4.3, SW4.4
RST: Pad_gge175063.1, U30.1
